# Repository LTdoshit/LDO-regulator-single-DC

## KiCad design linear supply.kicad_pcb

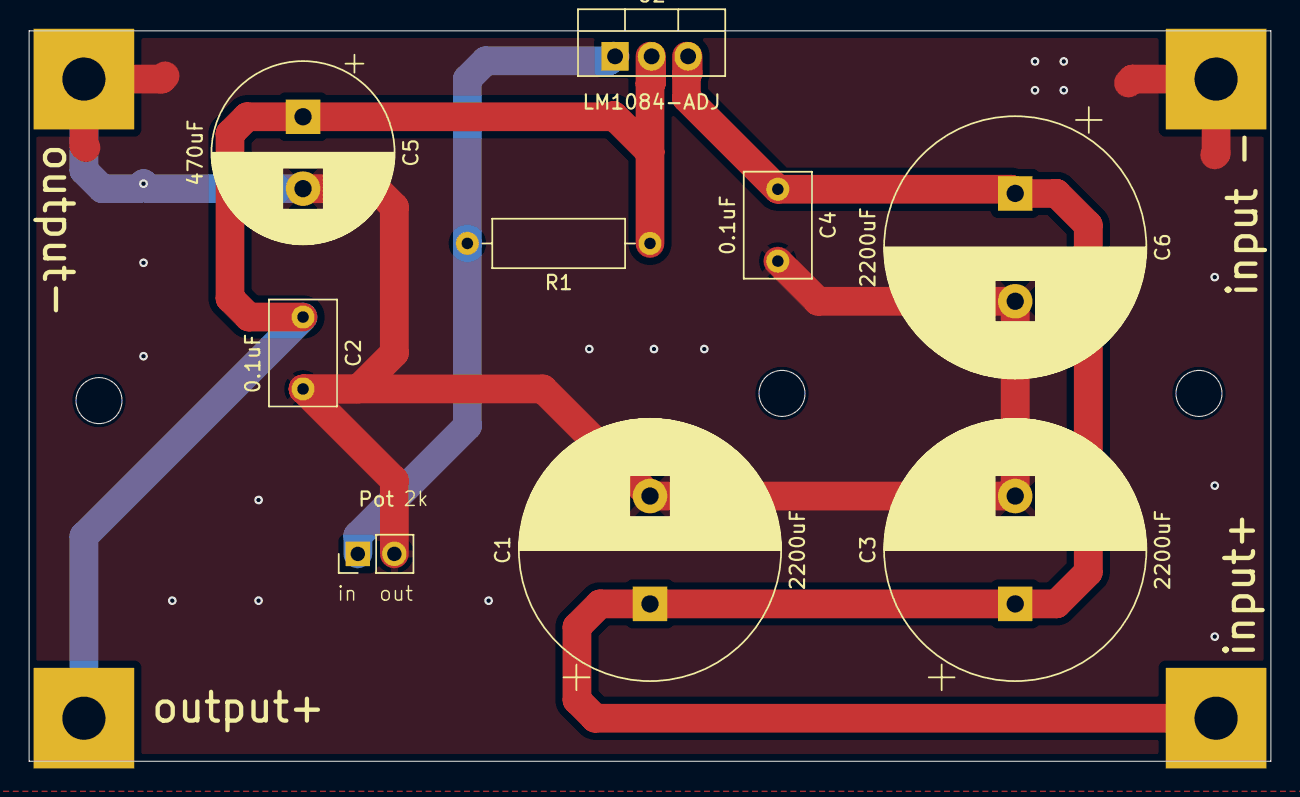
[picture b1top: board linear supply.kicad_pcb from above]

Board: 2 copper layers, 86.4 x 50.8 mm, 10 parts (0 on the bottom side), 4 nets.

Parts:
C1, C3, C6: 2200uF; CP_Radial_D18.0mm_P7.50mm
C2, C4: 0.1uF; C_Rect_L7.2mm_W4.5mm_P5.00mm_FKS2_FKP2_MKS2_MKP2
C5: 470uF; CP_Radial_D12.5mm_P5.00mm
Pot: PinHeader_1x02_P2.54mm_Vertical
R1: r=""; R_Axial_DIN0309_L9.0mm_D3.2mm_P12.70mm_Horizontal
U2: LM1084-ADJ; TO-220-3_Vertical
input -: SolderWire-0.1sqmm_1x01_D0.4mm_OD1mm

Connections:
DC+: C1.1, C3.1, C4.1, C6.1, U2.3 (VI)
DC-: C1.2, C2.2, C3.2, C4.2, C5.2, C6.2, Pot.2, input -.1
in pot: Pot.1, R1.2, U2.1 (ADJ)
out+: C2.1, C5.1, R1.1, U2.2 (VO)
